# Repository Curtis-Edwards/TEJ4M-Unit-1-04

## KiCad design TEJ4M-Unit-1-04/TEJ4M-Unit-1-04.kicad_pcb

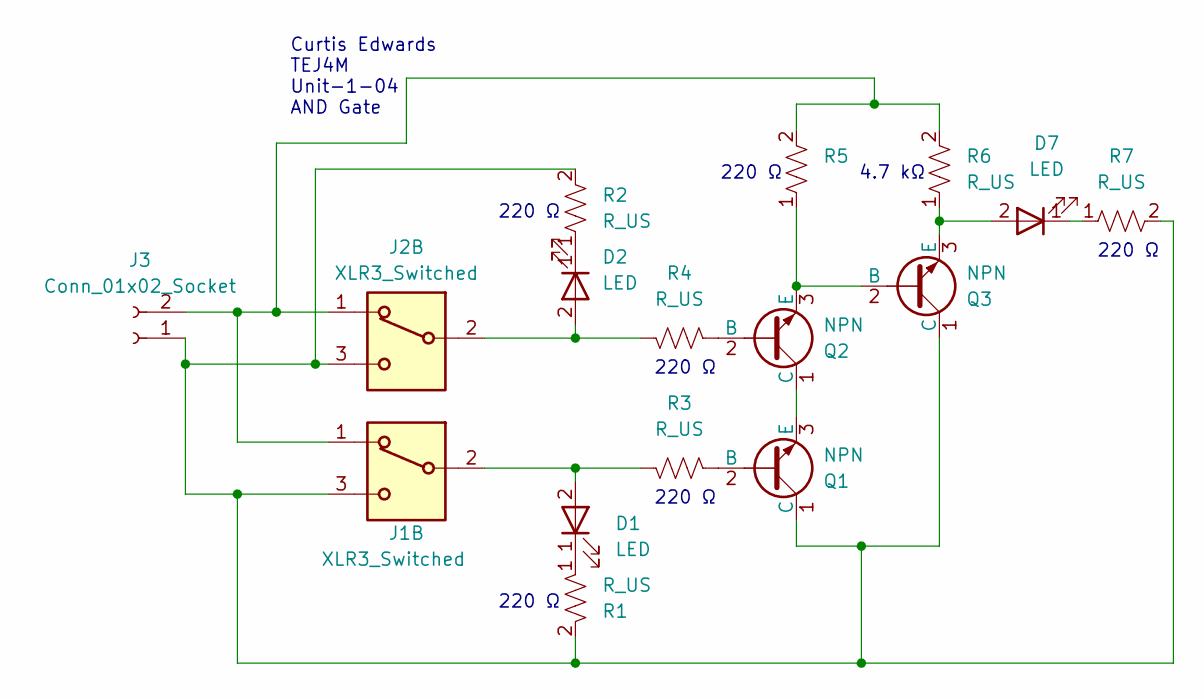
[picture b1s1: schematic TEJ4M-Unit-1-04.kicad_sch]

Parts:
D1, D2, D7: LED; LED_D3.0mm
J1, J2: XLR3_Switched; PinSocket_1x03_P2.54mm_Vertical
J3: Conn_01x02_Socket; PinSocket_1x02_P2.54mm_Vertical
Q1, Q2, Q3: NPN; TO-92
R1, R2, R3, R4, R5, R6, R7: R_US; R_Axial_DIN0204_L3.6mm_D1.6mm_P5.08mm_Horizontal

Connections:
unnamed: D1.2 (A), J1.2, R3.1
unnamed: D1.1 (K), R1.1
unnamed: D2.2 (A), J2.2, R4.1
unnamed: D2.1 (K), R2.1
unnamed: D7.2 (A), Q3.3 (E), R6.1
unnamed: D7.1 (K), R7.1
unnamed: J1.3, J2.3, J3.1, Q1.1 (C), Q3.1 (C), R1.2, R2.2, R7.2
unnamed: J1.1, J2.1, J3.2, R5.2, R6.2
unnamed: Q1.2 (B), R3.2
unnamed: Q1.3 (E), Q2.1 (C)
unnamed: Q2.2 (B), R4.2
unnamed: Q2.3 (E), Q3.2 (B), R5.1

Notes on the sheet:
220 Ω
4.7 kΩ
Curtis Edwards TEJ4M Unit-1-04 AND Gate

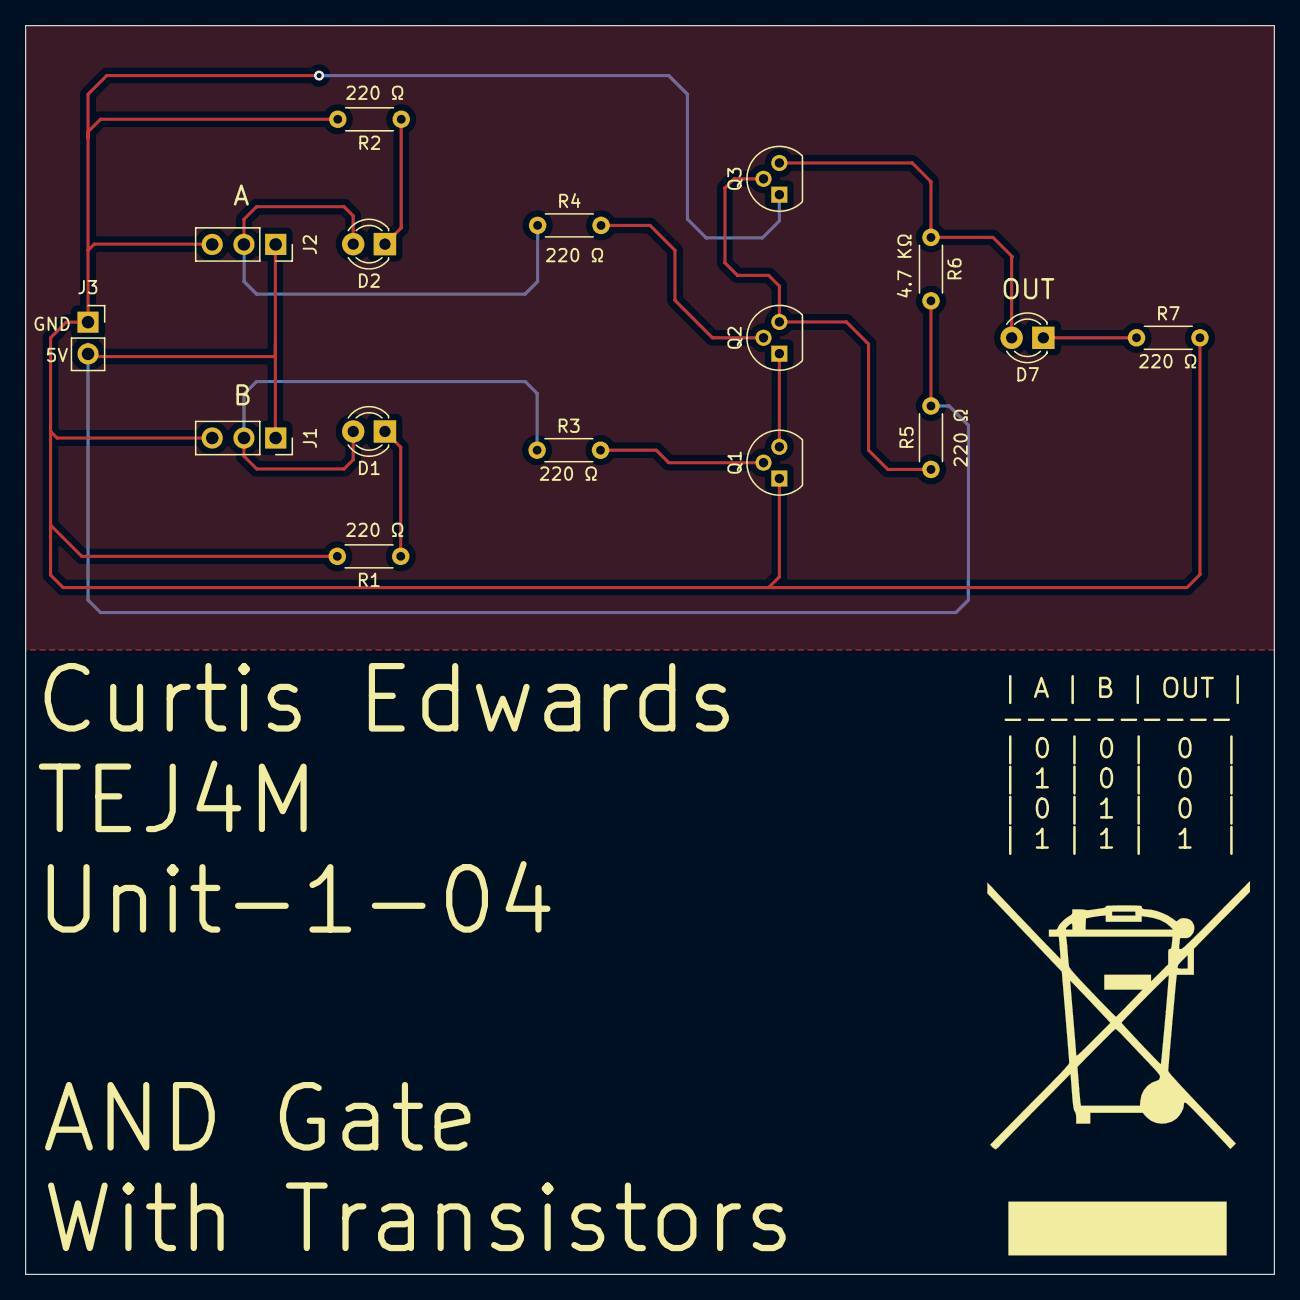
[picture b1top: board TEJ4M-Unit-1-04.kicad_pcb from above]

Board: 2 copper layers, 100.0 x 100.0 mm, 16 parts (0 on the bottom side), 12 nets.
